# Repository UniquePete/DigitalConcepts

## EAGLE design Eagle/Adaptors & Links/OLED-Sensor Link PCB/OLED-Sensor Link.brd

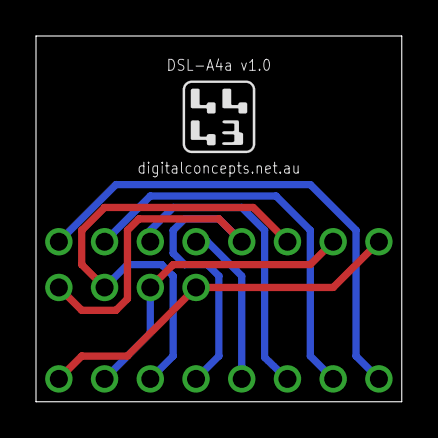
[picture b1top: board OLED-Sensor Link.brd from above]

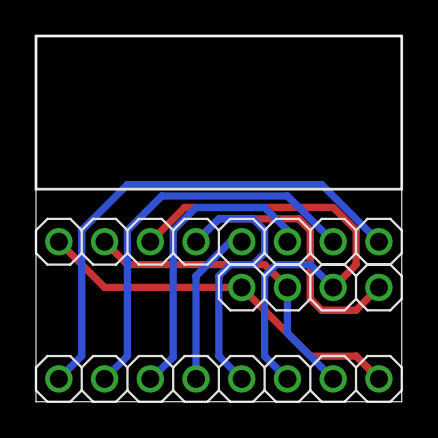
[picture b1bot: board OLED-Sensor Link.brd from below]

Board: 2 copper layers, 20.3 x 20.3 mm, 3 parts (3 on the bottom side), 8 nets.

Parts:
J1: BCS-A4a; CONN_08-GENERIC
J2: Sensor; CONN_08-GENERIC
J3: OLED Display; CONN_04-GENERIC

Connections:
unnamed: J1.8, J2.1, J3.1
unnamed: J1.7, J2.2, J3.2
unnamed: J1.6, J2.3, J3.3
unnamed: J1.5, J2.4, J3.4
unnamed: J1.4, J2.5
unnamed: J1.3, J2.6
unnamed: J1.2, J2.7
unnamed: J1.1, J2.8
